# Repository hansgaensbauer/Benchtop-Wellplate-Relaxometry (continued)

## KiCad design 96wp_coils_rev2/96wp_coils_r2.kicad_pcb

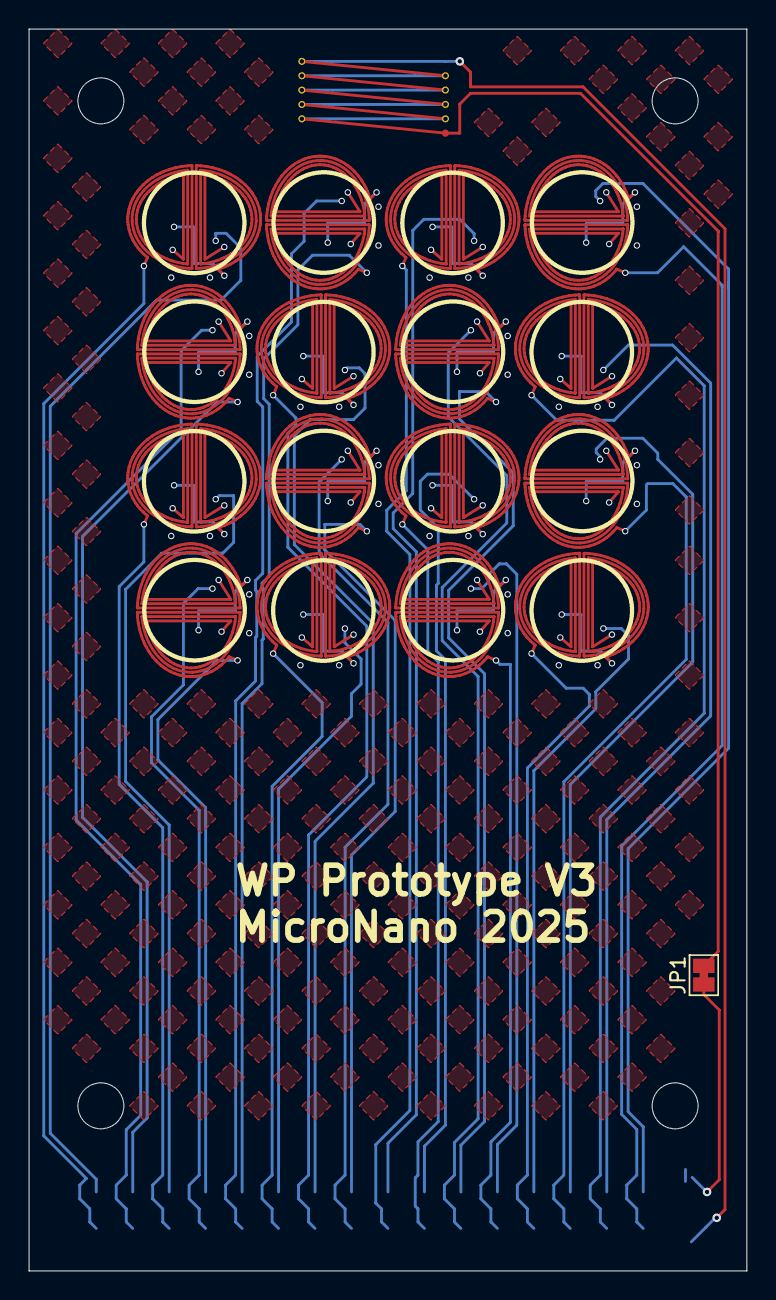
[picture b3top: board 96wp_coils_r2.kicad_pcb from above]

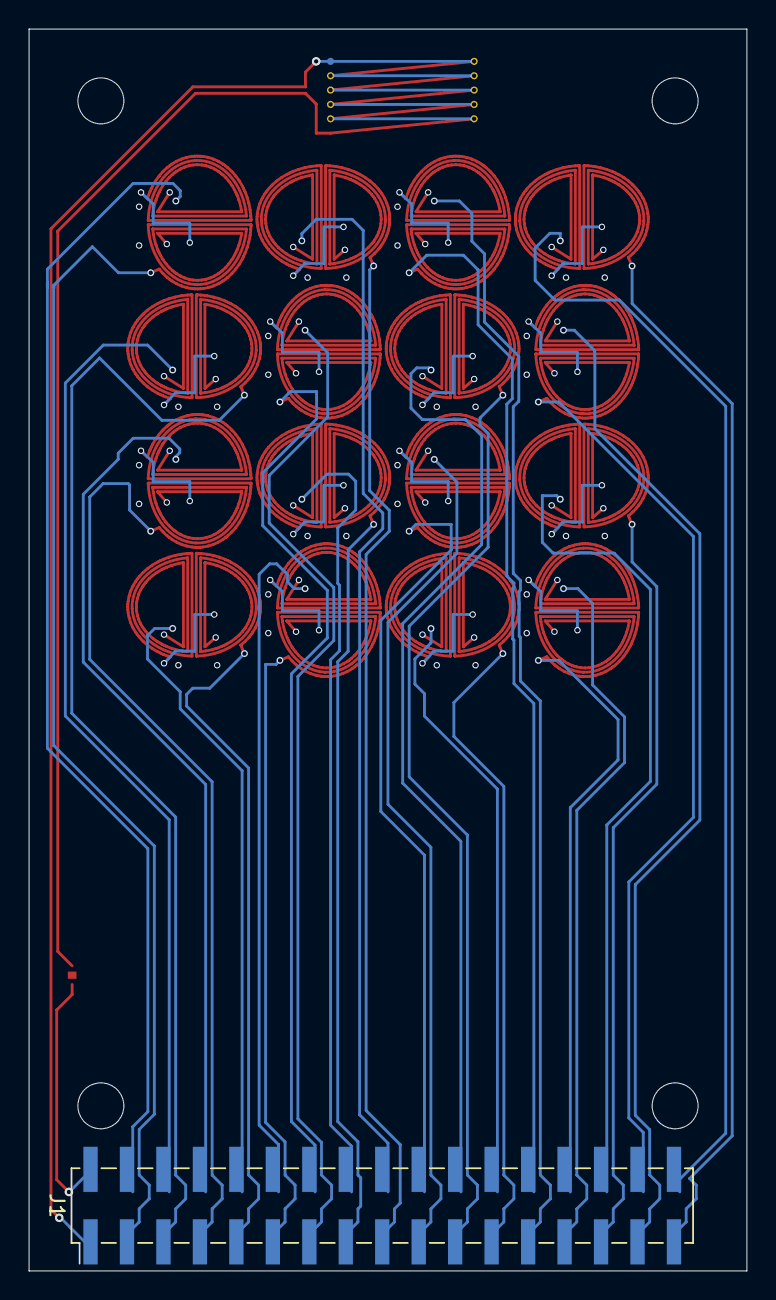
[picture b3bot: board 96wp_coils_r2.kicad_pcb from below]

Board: 4 copper layers, 50.0 x 86.5 mm, 19 parts (2 on the bottom side), 35 nets.

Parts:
J1: Conn_01x34; PinHeader_2x17_P2.54mm_Vertical_SMD
JP1: SolderJumper_2_Bridged; SolderJumper-2_P1.3mm_Bridged_Pad1.0x1.5mm
L1, L2, L3, L4, L5, L6, L7, L8, L9, L10, L11, L12, L13, L14, L15, L16: L_Small; 96WP_Surface_Coil
L17: L_Small; Field_Sense_Coil

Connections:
/C1+: J1.34, L1.1
/C1-: J1.33, L1.2
/C2+: J1.32, L2.2
/C2-: J1.31, L2.1
/C3+: J1.30, L3.1
/C3-: J1.29, L3.2
/C4+: J1.28, L4.2
/C4-: J1.27, L4.1
/C5+: J1.26, L5.2
/C5-: J1.25, L5.1
/C6+: J1.22, L6.1
/C6-: J1.21, L6.2
/C7+: J1.20, L7.2
/C7-: J1.19, L7.1
/C8+: J1.24, L8.1
/C8-: J1.23, L8.2
/C9+: J1.18, L9.1
/C9-: J1.17, L9.2
/C10+: J1.14, L10.2
/C10-: J1.13, L10.1
/C11+: J1.16, L11.1
/C11-: J1.15, L11.2
/C12+: J1.12, L12.1
/C12-: J1.11, L12.2
/C13+: J1.4, L13.1
/C13-: J1.3, L13.2
/C14+: J1.5, L14.1
/C14-: J1.6, L14.2
/C15+: J1.8, L15.1
/C15-: J1.7, L15.2
/C16+: J1.10, L16.1
/C16-: J1.9, L16.2
/F+: J1.2, L17.1
/F-: J1.1, JP1.1 (A)
unnamed: JP1.2 (B), L17.2

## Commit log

2026-05-05 Add photo of wellplate hardware
